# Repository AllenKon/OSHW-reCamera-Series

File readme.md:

# Introduction

**reCamera** is an open source AI camera. The project provides a convenient solution for people who use custom DIY cameras.The feature of this project is that not only does the **RISC-V** system provide an AI recognition solution for edge cameras, but we also open source the related application projects of the camera and the model design of the electronic circuit and 3D shell. We provide a **model transformation tool**, users can quantify and transplant the traditional recognition model according to their needs. In addition, we reserve all interfaces of the processor, and users can personalize the external interfaces according to their projects and requirements.

## reCamera Core

reCamera Core is a core module design based on SG2002 open source chip.
SG2002 equipped with high-performance RISC-V and ARM cores, it provides a fully open-source, ecosystem-rich deep learning vision processor that delivers 1.0 TOPS computing power@INT8.

As the name suggests, this is an open source camera core board. The core board contains the core processor, EMMC storage, and WiFi chip. The core module led all the pins of the processor out through two BtoB sockets.
Through this interface, junior electronics engineers can customize their exclusive cameras by designing SensorBoard and BaseBoard.

## Application:

### [reCamera Gimbal](https://github.com/AllenKon/Seeed_reCamera_Gimbal)

Open source Gimbal solution made using reCamera.

### [reCamera Robot Arm]()

waiting...

## SensorBoard

| Board         | Features                           | To do list                                                   |
| ------------- | ---------------------------------- | ------------------------------------------------------------ |
| [S1_OV5647](./S1_OV5647/) | 500w pixels  <br />Rolling Shutter | Home Surveillance<br />PTZ Camera<br />Handheld Camera       |
| S2_IMX335     | 500w pixels  <br />Rolling Shutter | Machine Vision Systems<br />Robot<br />Biometrics            |
| S3_SC130GS    | 100w pixels<br />Global Shutter    | Machine Vision Systems,<br />IoT Camera,<br />Industrial Camera |

### S1_OV5647

> overview
> 

>schematic

> features:

<div>

<table ><tbody>
<tr >
    <td >SENSOR</td>
    <td class="dbon">ov5647</td>
    <td class="dbon">CMOS SIZE</td>
    <td class="dbon">1/4 inch</td>
</tr>
<tr >
    <td class="dbon">PIXELS</td>
    <td class="dbon">5MP</td>
    <td class="dbon">APERTURE</td>
    <td class="dbon">F2.4</td>
</tr>
<tr >
    <td >FOCAL LENGTL</td>
    <td class="dbon">3.89mm</td>
    <td class="dbon">FIELD OF VIEW</td>
    <td >72.9°</td>
</tr>
<tr >
    <td >DISTORTION</td>
    <td >&lt;1.5%</td>
    <td >DEPTH OF FIELD</td>
    <td >20cm ~∞</td>
</tr>
<tr >
    <td >IMAGE</td>
    <td  colspan="3">2592 x 1944 still picture resolution</td>
</tr>
<tr >
    <td >VIDEO</td>
    <td  colspan="3">1920 x 1080p @30, 1280 x 720p @60, 640 x 480p @60, 640 x 480p @90</td>
</tr></tbody>
</table>
</div>

- 4 x LED fill lights
- 1 x microphone
- 1 x speaker
- 3 x LED indicator

### S2_IMX335
> overview

>schematic

> features:

### S3_SC130GS

> overview

>schematic

> features:

## BaseBoard
### B1_Default

> overview
> 

>schematic

> features:

<div>

<table ><tbody>
<tr >
    <td >SENSOR</td>
    <td class="dbon">ov5647</td>
    <td class="dbon">CMOS SIZE</td>
    <td class="dbon">1/4 inch</td>
</tr>
<tr >
    <td class="dbon">PIXELS</td>
    <td class="dbon">5MP</td>
    <td class="dbon">APERTURE</td>
    <td class="dbon">F2.4</td>
</tr>
<tr >
    <td >FOCAL LENGTL</td>
    <td class="dbon">3.89mm</td>
    <td class="dbon">FIELD OF VIEW</td>
    <td >72.9°</td>
</tr>
<tr >
    <td >DISTORTION</td>
    <td >&lt;1.5%</td>
    <td >DEPTH OF FIELD</td>
    <td >20cm ~∞</td>
</tr>
<tr >
    <td >IMAGE</td>
    <td  colspan="3">2592 x 1944 still picture resolution</td>
</tr>
<tr >
    <td >VIDEO</td>
    <td  colspan="3">1920 x 1080p @30, 1280 x 720p @60, 640 x 480p @60, 640 x 480p @90</td>
</tr></tbody>
</table>
</div>

- 4 x LED fill lights
- 1 x microphone
- 1 x speaker
- 3 x LED indicator

### B2_POE

## Related Porjects:

[sscma Link](https://github.com/Seeed-Studio/sscma-example-sg200x)

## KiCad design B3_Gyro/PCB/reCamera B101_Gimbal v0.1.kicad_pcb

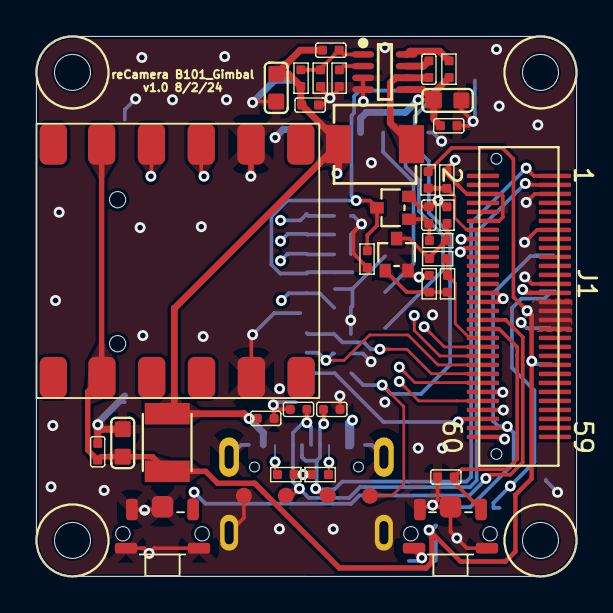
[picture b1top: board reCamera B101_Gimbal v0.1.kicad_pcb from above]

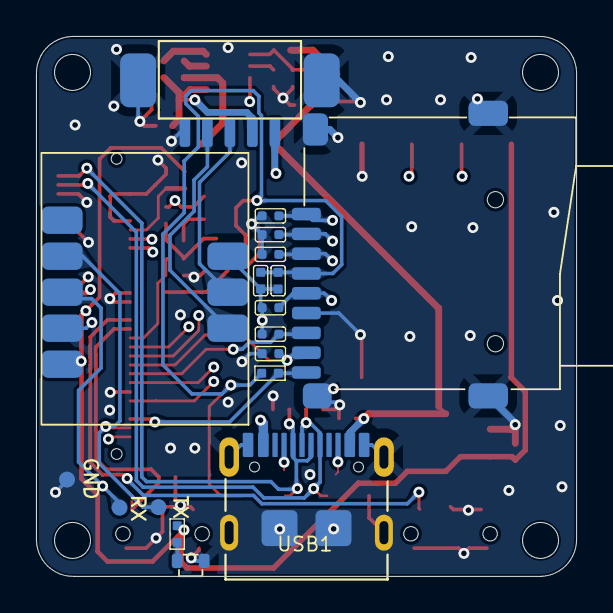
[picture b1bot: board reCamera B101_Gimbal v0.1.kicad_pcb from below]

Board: 4 copper layers, 30.0 x 30.0 mm, 58 parts (18 on the bottom side), 36 nets.

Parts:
C1: 1uF; C0402
C2, C3, C7, C8, C12: 100nF; C0402
C4, C11: 47uF; C0603
C5: 10nF; C0402
C6: 10uF; C0603
C9: 10pF; C0402
C10: 100pF; C0402
D1, D2, D3, D4, D5, D6, D7, D8, D9: ESDPSA0402V05; ESD-0402
D10: 27-21/GHC-YR1S2M/3C; LED2-0.6X1.7MM
F1: 2A; F1210
J1: ST-BTB-058060-A; BTB60-Male-Female-0.5-17.7x4.4mm
J2: ST-TF-003J; MICRO-SD-CARD-9P
J3: 1.25-5A-WT; JST5_2P_1d25_7_9x4_3x3_4mm
K1, K2: TD-1100AP-A4N-D1R; SW5-SMD-4.56X2.3X1.9MM
L1: 6.8uH
Q1: S9013W; SOT-323
Q2: CJ2101; SOT-323
R1: 510R; R0402
R2, R24: 1K; R0402
R3, R9, R21, R23: 100K; R0402
R4: 10K; R0402
R5: 20K; R0402
R6: 200k; R0402
R7, R12: 5.1K; R0402
R8: 10k; R0402
R10: 13.7k; R0402
R20: 47K; R0402
R22: 33K; R0402
TP1, TP2, TP3, TP4, TP5, TP6, TP7: Test Point; TP-D35MIL
U1: WT9011G4K
U2: TTL-CAN
U4: SY8303AIC
USB1: USB2.0 Type C; USB2.0-TYPE-C

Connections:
+3V3: C8.1, J1.27, Q2.2 (S), R22.2
+5V: C10.1, C11.1, C12.1, D1.1, F1.2, J3.1, L1.2, R9.2, USB1.A4_B9 (A4/B9/VBUS), USB1.B4_A9 (B4/A9/VBUS)
+12V: C3.1, C4.1, J3.2, R8.1, U4.5 (IN)
CANH: J3.4, U2.8 (CANH)
CANL: J3.3, U2.7 (CANL)
DEBUG_UART0_RX: J1.60, TP2.1 (T), U2.3 (R)
DEBUG_UART0_TX: J1.58, TP1.1 (T), U2.2 (T)
GND: C1.2, C2.2, C3.2, C4.2, C6.2, C7.2, C9.2, C11.2, C12.2, D1.2, D2.2, D3.2, D4.2, D5.2, D6.2, D7.2, D8.2, D9.2, D10.2 (-), J1.5, J1.6, J1.12, J1.13, J1.25, J1.28, J1.30, J1.50, J1.54, J2.S1 (SHD1), J2.S2 (SHD2), J2.S3 (SHD3), J2.S4 (SHD4), J2.T6 (VSS), J3.5, J3.6, J3.7, K1.2, K1.S1, K1.S2, K1.S3, K2.2, K2.S1, K2.S2, K2.S3, Q1.2 (E), R3.1, R4.1, R6.1, R7.1, R10.1, R12.2, R21.1, TP3.1 (T), TP6.1 (T), U1.5 (GND), U1.11 (GND), U2.4 (GND), U2.6 (GND), U4.3 (GND), U4.4 (GND), USB1.A1_B12 (A1/B12/GND), USB1.B1_A12 (B1/A12/GND), USB1.S1, USB1.S2, USB1.S3, USB1.S4, USB1.S5, USB1.S6
IIC1_SCL: J1.18, U1.9 (SCL)
IIC1_SDA: J1.16, U1.10 (SDA)
unnamed: D10.1 (+), R1.1
unnamed: Q1.1 (B), R2.2, R3.2
unnamed: Q1.3 (C), R20.1, R22.1, R24.1
unnamed: C8.2, Q2.1 (G), R20.2
unnamed: C5.2, U4.7 (BS)
unnamed: R8.2, U4.8 (EN)
unnamed: C10.2, R9.1, R10.2, U4.1 (FB)
unnamed: R6.2, U4.2 (FS)
unnamed: C5.1, L1.1, U4.6 (LX)
unnamed: R12.1, USB1.A5 (A5/CC1)
unnamed: R7.2, USB1.B5 (B5/CC2)
SD0_PWR_EN: J1.38, R2.1, R24.2
SDIO_CD/3V3: J1.56, J2.G1 (SWITCH), R23.1
SDIO_CLK/3V3: D6.1, J1.52, J2.T5 (CLOCK)
SDIO_CMD/3V3: D7.1, J1.48, J2.T3 (CMD)
SDIO_D0/3V3: D5.1, J1.46, J2.T7 (DAT0)
SDIO_D1/3V3: D4.1, J1.44, J2.T8 (DAT1)
SDIO_D2/3V3: D9.1, J1.42, J2.T1 (DAT2)
SDIO_D3/3V3: D8.1, J1.40, J2.T2 (CD/DAT3)
SD_PWR_3V3: C1.1, C2.1, J2.T4 (VDD), Q2.3 (D), R21.2, R23.2, TP7.1 (T)
UPGRAD_KEY/WL_BT_EN: C9.1, J1.36, K2.1
USB_DET: J1.14, R4.2, R5.1
USB_DN: D2.1, J1.1, TP4.1 (T), USB1.A7 (A7/DN1), USB1.B7 (B7/DN2)
USB_DP: D3.1, J1.3, TP5.1 (T), USB1.A6 (A6/DP1), USB1.B6 (B6/DP2)
VIN: C6.1, C7.1, F1.1, J1.29, J1.31, J1.33, J1.35, R1.2, R5.2, U1.2 (VCC), U1.8 (VCC), U2.5 (VCC)
nRESET: J1.34, K1.1

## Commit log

2024-08-09 Create re
2024-08-09 Rename 企业微信截图_1723175046695.png to B1_Default.png
